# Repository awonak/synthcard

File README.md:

# SynthCard

Synth Card for Adam Wonak

This synthcard is a circuit inspired by [Hagiwo's](https://www.youtube.com/@HAGIWO) SyncLFO and Bezier Curve, and the [Modulove](https://modulove.io/) MVMNT. I chose this design because of the seemingly endless creative firmware scripts I have written for the [Modulove Sync LFO](https://awonak.github.io/HagiwoModulove/synclfo/), so I wanted to make a business card to highlight this circuit design with some fun tweaks.

This is an iteration of the [SynthCard.com](https://synthcard.com) community from [Benjie Jiao](https://github.com/benjiao). 

## Demo Videos

4 Step Sequencer - https://youtu.be/5_vGYVA8IQ8

ADSR - https://youtu.be/wfQtB7HLKf4

## Synth Card Built by Friends 

[[@benjiaomodular](https://www.youtube.com/@benjiaomodular)] - https://youtube.com/shorts/xnUs8CACG_8

[[@bildpunkt](http://on.soundcloud.com/M9RUxw48PaAXDL477)] - https://youtu.be/3e_gjm9oc40

## Bill of Materials

To assist with assembly, you can use the interactive [ibom.html page](https://htmlpreview.github.io/?https://github.com/awonak/synthcard/blob/main/hardware/bom/ibom.html) to view a part placement guide.

| Reference(s) | Qty | Value | Supplier Link |
|-|-|-|-|
| C1, C2, C3, C4, C5 | 5 | 0.1uF Capacitor  | https://www.mouser.com/ProductDetail/594-K104M15X7RF53L2 |
| C6 | 1 | 4.7uF Capacitor | https://www.mouser.com/ProductDetail/810-FG14X5R1H475KRT6 |
| D1, D2, D3, D4, D5, D6 | 6 | 1N5817 Schottky Diode | https://www.mouser.com/ProductDetail/833-1N5817-TP |
| D7 | 1 | 3MM LED | https://www.mouser.com/ProductDetail/604-WP3A8ID |
| R1, R2, R3, R4 | 4 | 1K Resistor | https://www.mouser.com/ProductDetail/660-MF1-4DCT52R1001F |
| R11, R12, R13, R14 | 4 | 1K Resistor (LED Brightness) | https://www.mouser.com/ProductDetail/660-MF1-4DCT52R1001F |
| R5, R7 | 2 | 10k Resistor | https://www.mouser.com/ProductDetail/660-MF1-4DCT52R1002F |
| R6, R8 | 2 | 100k Resistor | https://www.mouser.com/ProductDetail/660-MF1-4D52R1003F |
| R9 | 1 | 22k Resistor | https://www.mouser.com/ProductDetail/660-MF1-4DCT52R2202F |
| R10 | 1 | 470 Resistor | https://www.mouser.com/ProductDetail/660-MF1-4DCT52R4700F |
| VR1, VR2, VR3, VR4 | 4 | 20MM Slide Potentiometer 100K | https://www.mouser.com/ProductDetail/652-PTL20-15R0-104B1 |
| J3, J4, J5 | 1 | Thonkiconn 3.5mm Mono Jack | https://www.thonk.co.uk/shop/thonkiconn/ |
| A1 | 1 | Arduino Nano | [https://www.amazon.com/...](https://www.amazon.com/LAFVIN-Board-ATmega328P-Micro-Controller-Arduino/dp/B07G99NNXL/ref=sr_1_1_sspa?crid=110SU9VW3VQB6&keywords=arduino+nano&qid=1703001737&sprefix=arduino+nano%2Caps%2C117&sr=8-1-spons&sp_csd=d2lkZ2V0TmFtZT1zcF9hdGY&psc=1) |

## Pinout

| Arduino Pin | Function |
|-|-|
| A0 | Slider 1 Input |
| A1 | Slider 2 Input |
| A2 | Slider 3 Input |
| A3 | Slider 4 Input |
| A7 | Analog Input |
| D3 | Slider 4 LED |
| D5 | Slider 3 LED |
| D6 | Slider 2 LED |
| D9 | Slider 1 LED |
| D10 | Digital Output |
| D11 | Digital Input |

## Code Example

The most basic program we can write for the Synth Card is a Blink program. Using the pin guide above, we can see the digital output is `D10` which has an LED connected to the circuit. We can use this pin to blink the LED. 

```cpp
#define CV_OUT 10  // CV Output with LED

void setup() {
  pinMode(CV_OUT, OUTPUT);
}

void loop() {
  digitalWrite(CV_OUT, HIGH);
  delay(500);
  digitalWrite(CV_OUT, LOW);
  delay(500);
}
```

To test out all of the inputs, outputs, and LEDs, you can flash the [HardwareTest](firmware/HardwareTest/HardwareTest.ino) script.

To see additional example firmware scripts, head over to [firmware](firmware/).

## Hardware Revision History

| Revision | Date | Notes
|-|-|-|
| ver0.3 | 2024-01-07 | - Change: minor silkscreen updates<br> - Change: made 5v trace larger
| ver0.2 | 2023-12-28 | - Fix: CV Output circuit was backwards<br> - Change: Rename capacitor footprint values<br> - Change: Improved LED footprint values<br> - Change: Add linktr.ee and social logos 
| ver0.1 | 2023-12-18 | Initial release

## Enclosure

* Case: [OnShape 3D printer case design](https://cad.onshape.com/documents/56a3cdf5a05401551b0a6543/v/da0e57abf21331cdf97fa6e6/e/f128ee10c6516a251dc2fe2a)
* Cover: [OnShape 3D printer cover design](https://cad.onshape.com/documents/eee74bc148d4d859dd74c709/w/c0c5180a8fda910a15efede6/e/bb4b46e599de372330158219?renderMode=0&uiState=681d00e47421d42a91637a86) (Designed by [BbartokK](https://bbartokk.bandcamp.com/))

## Buy a SynthCard Kit

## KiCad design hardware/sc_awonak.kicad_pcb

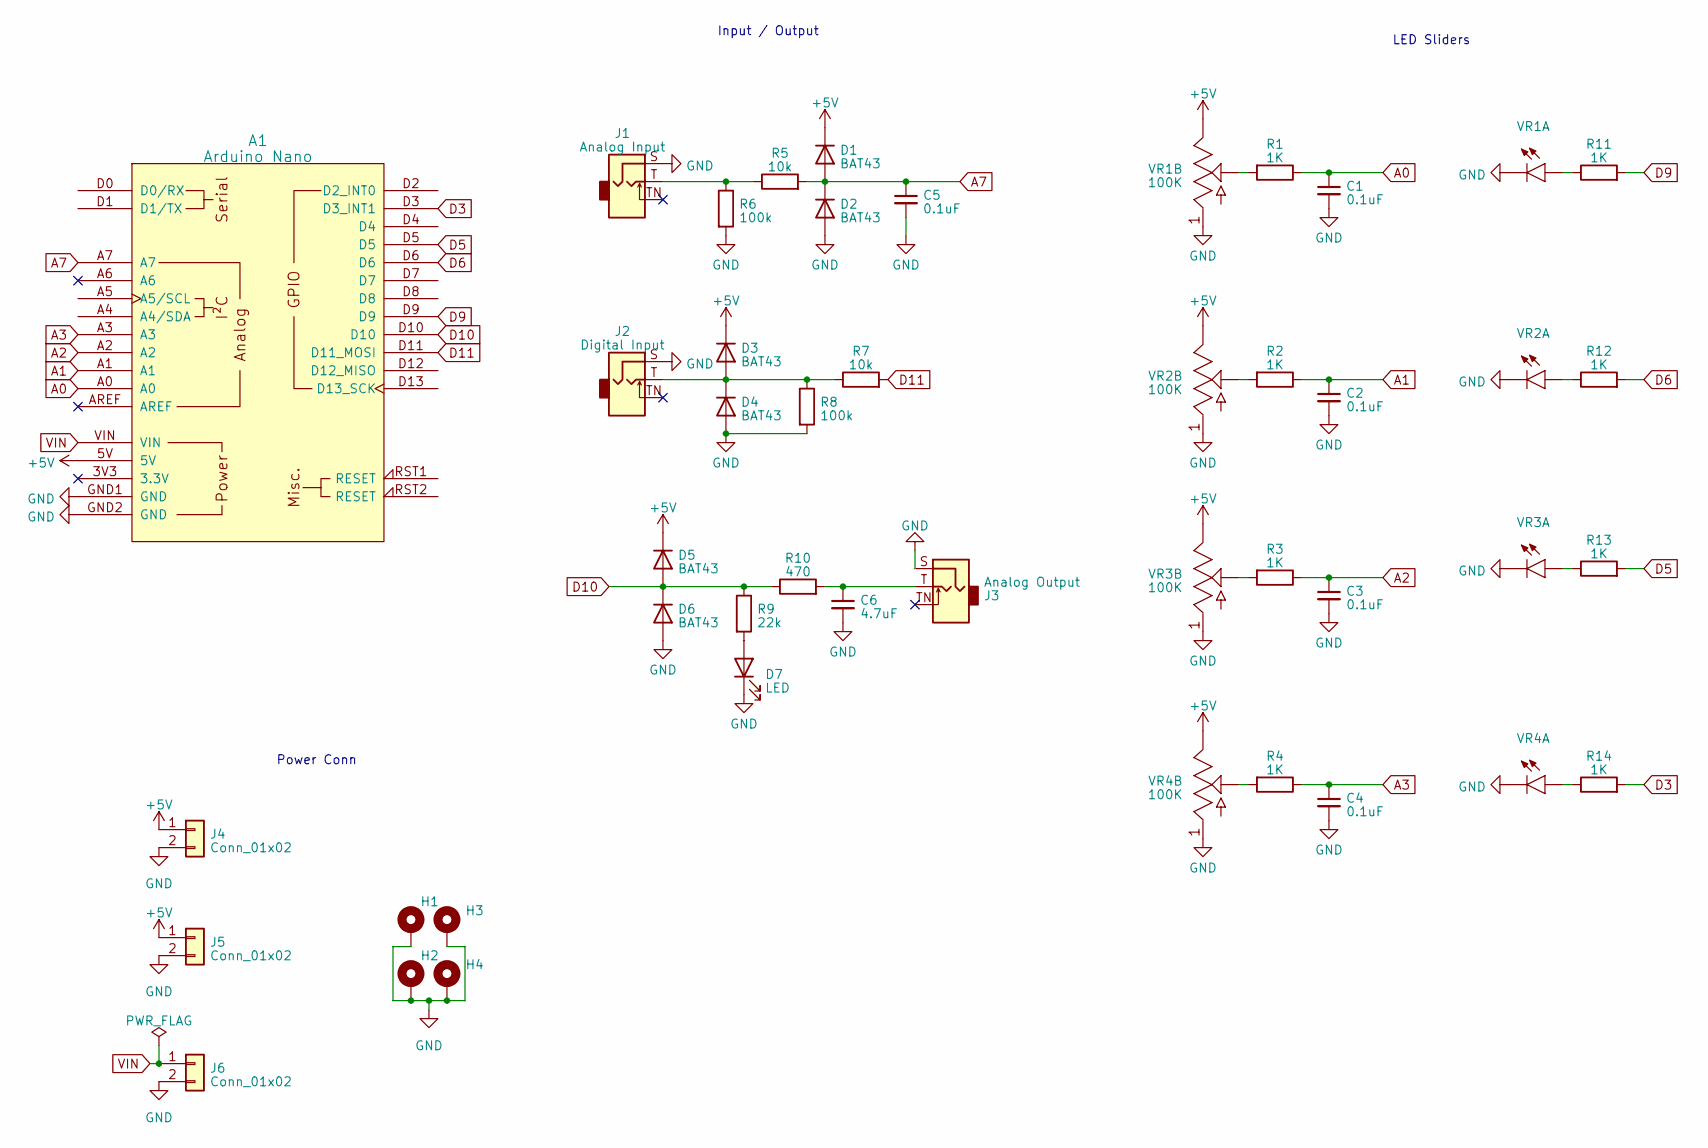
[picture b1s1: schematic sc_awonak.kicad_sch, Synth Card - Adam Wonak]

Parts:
A1: Arduino Nano; Arduino_Nano_Socket
C1, C2, C3, C4, C5: 0.1uF; C_Disc_D3.0mm_W2.0mm_P2.50mm
C6: 4.7uF; C_Disc_D3.0mm_W2.0mm_P2.50mm
D1, D2, D3, D4, D5, D6: BAT43; D_DO-35_SOD27_P7.62mm_Horizontal
D7: LED; LED_D3.0mm
H1, H2, H3, H4: MountingHole_Pad; MountingHole_3.2mm_M3_Pad
J1: Analog Input; Jack_3.5mm_QingPu_WQP-PJ398SM_Vertical_CircularHoles
J2: Digital Input; Jack_3.5mm_QingPu_WQP-PJ398SM_Vertical_CircularHoles
J3: Analog Output; Jack_3.5mm_QingPu_WQP-PJ398SM_Vertical_CircularHoles
J4, J5, J6: Conn_01x02; PinHeader_1x02_P2.54mm_Horizontal
R1, R2, R3, R4, R11, R12, R13, R14: 1K; R_Axial_DIN0207_L6.3mm_D2.5mm_P7.62mm_Horizontal
R5, R7: 10k; R_Axial_DIN0207_L6.3mm_D2.5mm_P7.62mm_Horizontal
R6, R8: 100k; R_Axial_DIN0207_L6.3mm_D2.5mm_P7.62mm_Horizontal
R9: 22k; R_Axial_DIN0207_L6.3mm_D2.5mm_P7.62mm_Horizontal
R10: 470; R_Axial_DIN0207_L6.3mm_D2.5mm_P7.62mm_Horizontal
VR1, VR2, VR3, VR4: 100K; Pot_Slider_LED_20mm_RA2045F

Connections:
+5V: A1.5V, D1.1 (K), D3.1 (K), D5.1 (K), J4.1, J5.1, VR1.P3 (3), VR2.P3 (3), VR3.P3 (3), VR4.P3 (3)
A0: A1.A0, C1.1, R1.1
A1: A1.A1, C2.1, R2.1
A2: A1.A2, C3.1, R3.1
A3: A1.A3, C4.1, R4.1
A7: A1.A7, C5.1, D1.2 (A), D2.1 (K), R5.2
D3: A1.D3 (D3_INT1), R14.2
D5: A1.D5, R13.2
D6: A1.D6, R12.2
D9: A1.D9, R11.2
D10: A1.D10, D5.2 (A), D6.1 (K), R9.1, R10.1
D11: A1.D11 (D11_MOSI), R7.2
GND: A1.GND1 (GND), A1.GND2 (GND), C1.2, C2.2, C3.2, C4.2, C5.2, C6.2, D2.2 (A), D4.2 (A), D6.2 (A), D7.1 (K), H1.1, H2.1, H3.1, H4.1, J1.S, J2.S, J3.S, J4.2, J5.2, J6.2, R6.2, R8.2, VR1.LEDC (C), VR1.P1 (1), VR2.LEDC (C), VR2.P1 (1), VR3.LEDC (C), VR3.P1 (1), VR4.LEDC (C), VR4.P1 (1)
unnamed: C6.1, J3.T, R10.2
unnamed: D3.2 (A), D4.1 (K), J2.T, R7.1, R8.1
unnamed: D7.2 (A), R9.2
unnamed: J1.T, R5.1, R6.1
unnamed: R11.1, VR1.LEDA (A)
unnamed: R1.2, VR1.P2 (2)
unnamed: R12.1, VR2.LEDA (A)
unnamed: R2.2, VR2.P2 (2)
unnamed: R13.1, VR3.LEDA (A)
unnamed: R3.2, VR3.P2 (2)
unnamed: R14.1, VR4.LEDA (A)
unnamed: R4.2, VR4.P2 (2)
VIN: A1.VIN, J6.1

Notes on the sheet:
Input / Output
LED Sliders
Power Conn

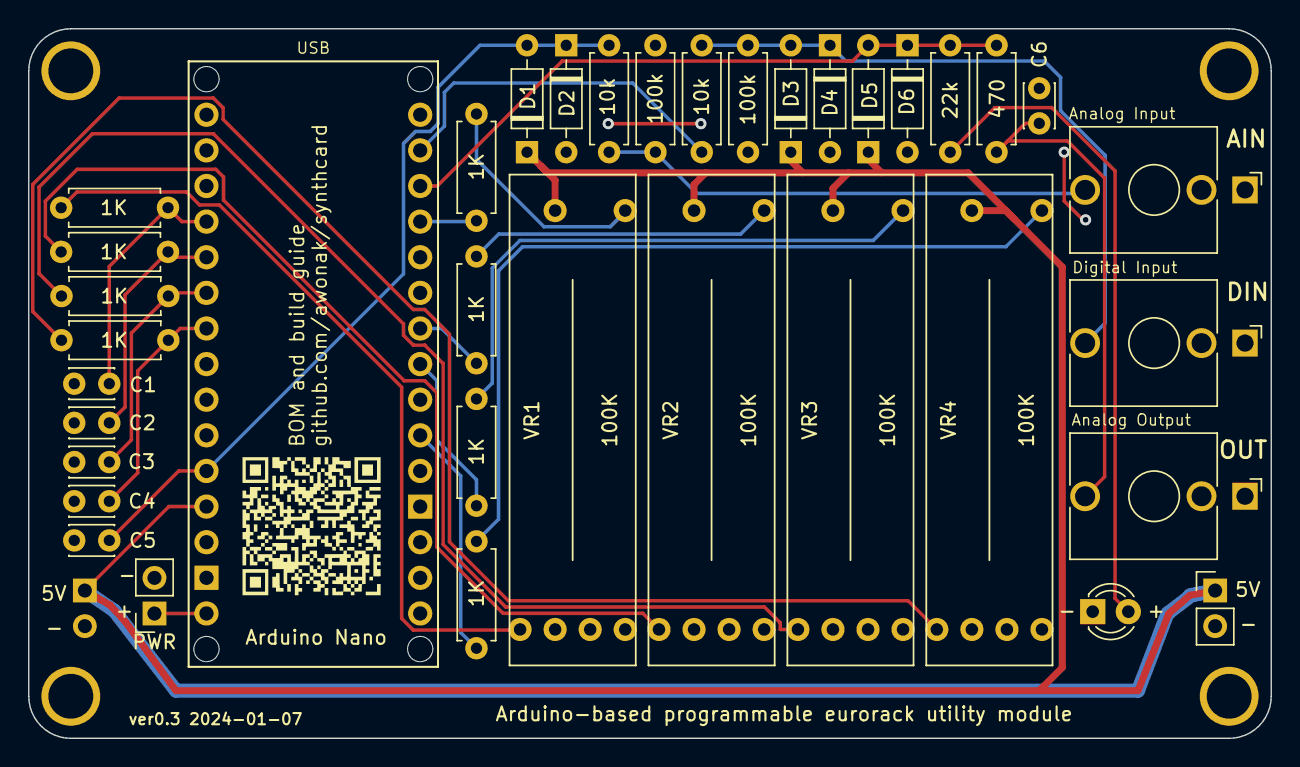
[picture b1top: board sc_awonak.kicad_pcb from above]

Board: 2 copper layers, 88.6 x 50.6 mm, 42 parts (1 on the bottom side), 26 nets.

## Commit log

2023-12-18 More revision updates and add preview image
2023-12-18 Added 3d rendering, schematic PDF, and more pcb revisions.
2023-12-19 Added BOM to README
2023-12-19 Add ibom and update gitignore
2023-12-19 README fixes
2023-12-20 Update README.md
    Fix resistor links for consistency. Add Arduino Pinout.
2023-12-29 rename schematic file
2023-12-29 hardware revision ver0.2
2023-12-29 Add revision changes to README and updated ibom.
2024-01-07 update a few silkscreen details. larger 5v trace. update ibom.
2024-01-07 Add default hardware testing script.
2024-01-07 add ver0.3 updates to readme
2024-01-08 Added Baby4 and ADSR example firmwares
2024-01-09 Update README.md
    Add demo video
2024-01-13 Add firmware example and links to README
2024-01-13 rename kicad project folder from sc_awonak to hardware.
2024-01-13 update hardware links in readme
2024-01-13 Update rendering images to match current revision. Add demo video.
2024-01-13 update 3d model of pcb editor view
2024-02-09 Update README.md
    Add link to synthcard.com and tindie link
2024-02-13 Update README.md
    typo
2024-02-16 Add enclosure link to readme
2024-02-17 Add sloped trigger delay script
2024-02-17 improve variable names
2024-05-30 update hardware files
2024-05-31 Update README.md
    New baby 4 video
2025-05-08 Update README.md
    Added link to a 3D Printable enclosure lid designed by BbartokK
